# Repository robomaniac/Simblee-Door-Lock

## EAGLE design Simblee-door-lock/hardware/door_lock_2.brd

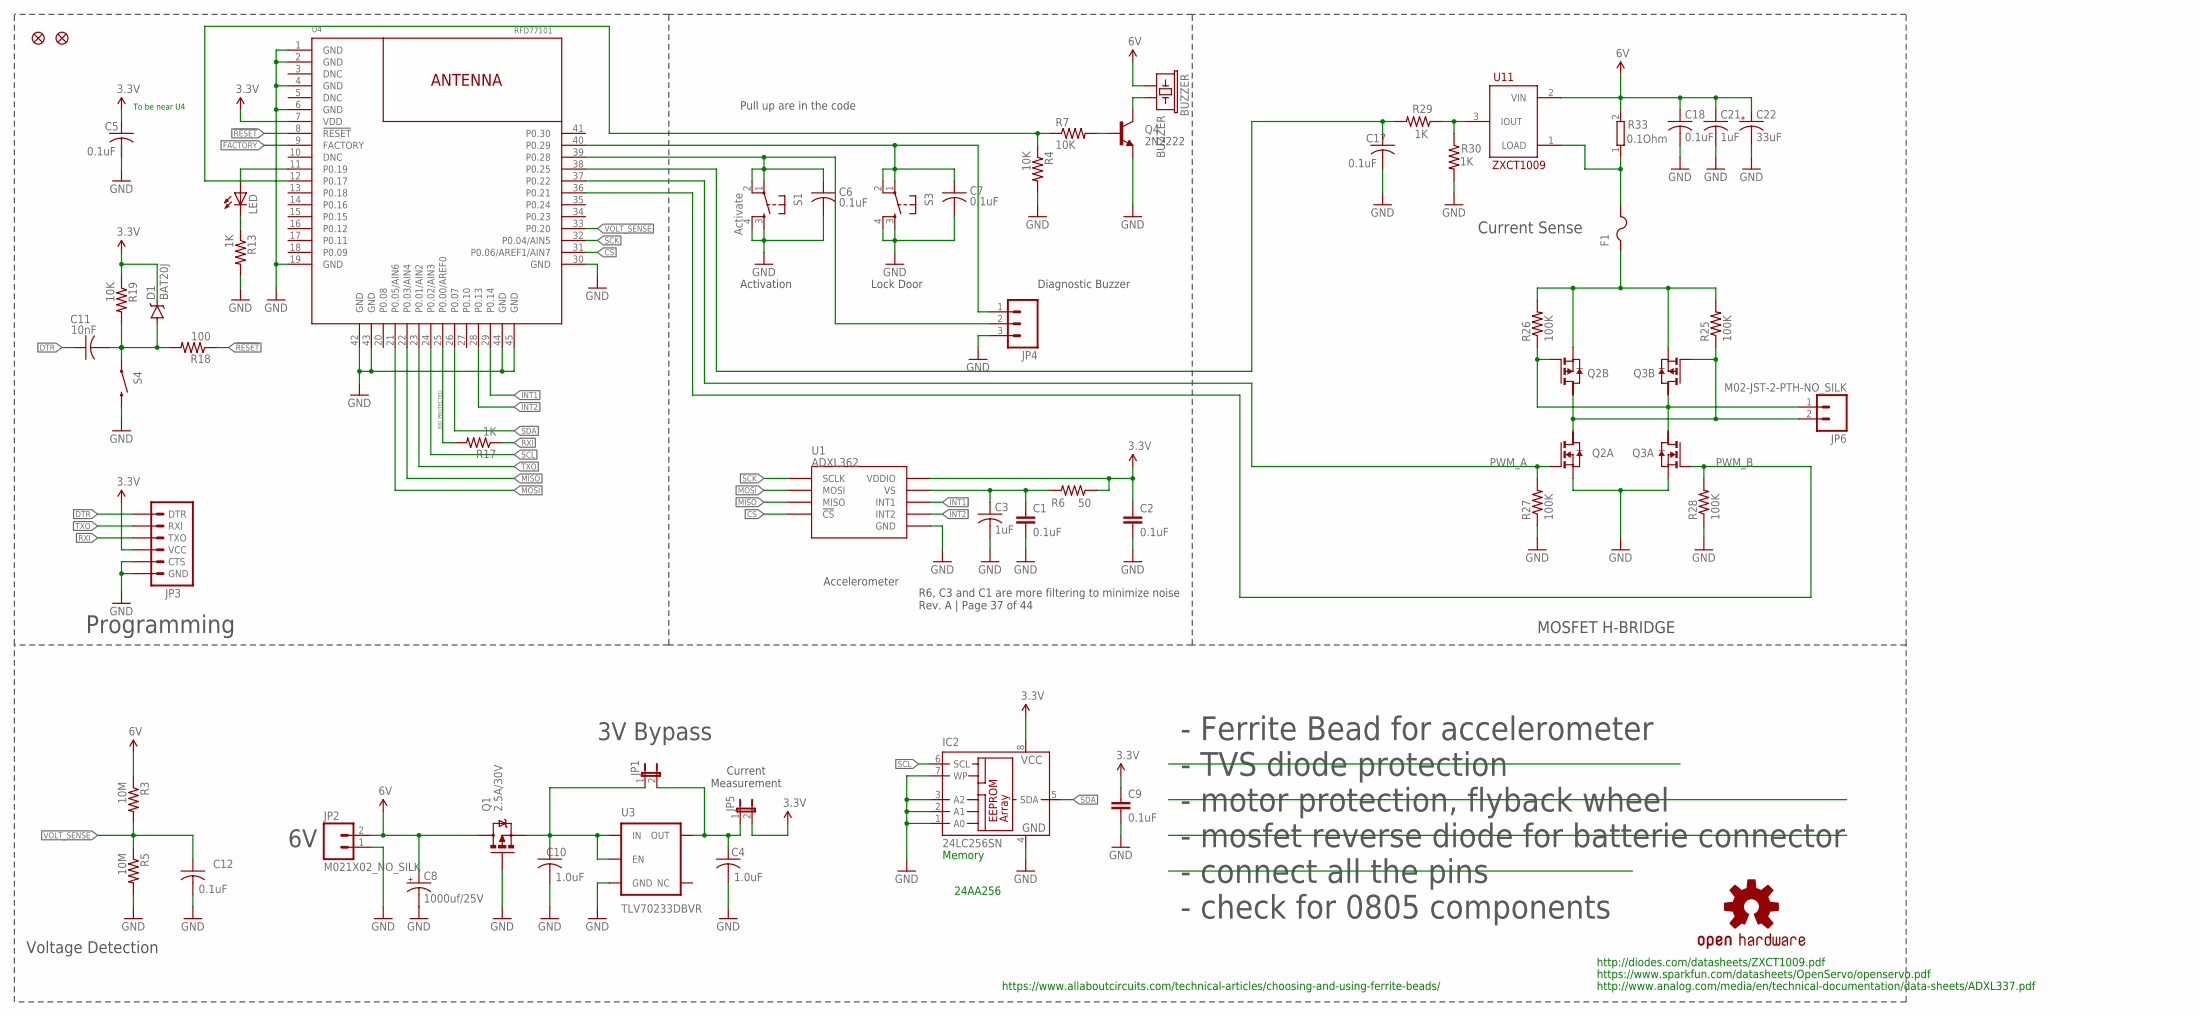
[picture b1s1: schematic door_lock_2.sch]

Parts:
BUZZER: BUZZER; BUZZER-12MM-NS
C1, C2, C9: 0.1uF; 0805
C3, C21: 1uF; C0805
C4, C10: 1.0uF; C0805
C5, C6, C7, C12, C17, C18: 0.1uF; C0805
C8: 1000uf/25V; CPOL-RADIAL-1000UF-25V-KIT
C11: 10nF; C0805
C22: 33uF; EIA3528
D1: BAT20J; SOD-323
F1: PTCFUSE-1812; 1812
IC2: 24LC256SN; SO-08
JP1: JUMPER-2SMD-NO; SJ_2S-NO
JP2: M021X02_NO_SILK; 1X02_NO_SILK
JP3: ARDUINO_SERIAL_PROGRAMPTH; 1X06
JP4: M03PTH; 1X03
JP5: JUMPER-2PTH; 1X02
JP6: M02-JST-2-PTH-NO_SILK; JST-2-PTH-NS
JP9, JP10: FIDUCIALUFIDUCIAL; MICRO-FIDUCIAL
LED: LEDCHIP-LED0805; CHIP-LED0805
Q1: 2.5A/30V; SOT23-3
Q2, Q3: PN_MOSFET-SO8; SO8
Q4: 2N2222; SOT23
R3, R5: 10M; R0805
R4, R7, R19: 10K; R0805
R6: 50; R0805
R13, R17, R29, R30: 1K; R0805
R18: 100; R0805
R25, R26, R27, R28: 100K; R0805
R33: 0.1Ohm; R1206W
S1: Activate; TACTILE-PTH
S3: TAC_SWITCHPTH; TACTILE-PTH
S4: SWITCH-MOMENTARY-2SMD; TACTILE-SWITCH-SMD
U1: ADXL362
U3: TLV70233DBVR; SOT23-5
U4: RFD77101
U11: ZXCT1009; SOT23-3
U$3: OSHW-LOGOS; OSHW-LOGO-S

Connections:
3.3V: C2.1, C5.1, C9.1, D1.C, IC2.8 (VCC), JP3.4 (VCC), JP5.2, R6.1, R19.1, U1.P$1 (VDDIO), U4.7 (VDD)
6V: BUZZER.+ (1), C8.+, C18.1, C21.1, C22.A (+), JP2.2, Q1.3 (D), R3.1, R33.2, U11.2 (VIN)
!RESET: R18.1, U4.8 (!RESET!)
ACTIVATE: C6.1, JP4.2, S1.1, S1.2, U4.39 (P0.28)
BUZZER: R4.1, R7.1, U4.12 (P0.17)
CS: U1.P$8 (!CS), U4.31 (P0.06/AREF1/AIN7)
CURSENSE: C17.1, R29.2, U4.38 (P0.25)
DTR: C11.1, JP3.1 (DTR)
FACTORY: U4.9 (FACTORY)
GND: C1.2, C2.2, C3.2, C4.2, C5.2, C6.2, C7.2, C8.-, C9.2, C10.2, C12.2, C17.2, C18.2, C21.2, C22.C (-), IC2.1 (A0), IC2.2 (A1), IC2.3 (A2), IC2.4 (GND), IC2.7 (WP), JP2.1, JP3.5 (CTS), JP3.6 (GND), JP4.3, Q1.1 (G), Q2.1 (S), Q3.1 (S), Q4.2 (E), R4.2, R5.2, R13.2, R27.1, R28.1, R30.2, S1.3, S1.4, S3.3, S3.4, S4.3 (2), U1.P$12 (GND), U1.P$13 (GND), U1.P$16 (GND), U3.2 (GND), U4.1 (GND), U4.2 (GND), U4.4 (GND), U4.6 (GND), U4.19 (GND), U4.30 (GND), U4.42 (GND), U4.43 (GND), U4.44 (GND), U4.45 (GND)
INT1: U1.P$11 (INT1), U4.29 (P0.14)
INT2: U1.P$9 (INT2), U4.28 (P0.13)
LOCK: C7.1, JP4.1, S3.1, S3.2, U4.40 (P0.29)
MISO: U1.P$7 (MISO), U4.22 (P0.03/AIN4)
MOSI: U1.P$6 (MOSI), U4.21 (P0.05/AIN6)
MOTOR_OUT_A: JP6.1, Q2.4 (G), Q3.5 (D), Q3.7 (D), R26.1
MOTOR_OUT_B: JP6.2, Q2.5 (D), Q2.7 (D), Q3.4 (G), R25.1
unnamed: C4.1, JP1.2, JP5.1, U3.5 (OUT)
unnamed: F1.2, R33.1, U11.1 (LOAD)
unnamed: C1.1, C3.1, R6.2, U1.P$14 (VS)
unnamed: Q4.1 (B), R7.2
unnamed: BUZZER.- (2), Q4.3 (C)
unnamed: C11.2, D1.A, R18.2, R19.2, S4.1
unnamed: LED.C, R13.1
unnamed: F1.1, Q2.3 (S), Q3.3 (S), R25.2, R26.2
unnamed: R29.1, R30.1, U11.3 (IOUT)
P0.10: LED.A, U4.11 (P0.19)
PWM_A: Q2.2 (G), R27.2, U4.37 (P0.22)
PWM_B: Q3.2 (G), R28.2, U4.36 (P0.21)
RXI: JP3.3 (TXO), R17.1
RXI_PROTECTED: R17.2, U4.25 (P0.00/AREF0)
SCK: U1.P$4 (SCLK), U4.32 (P0.04/AIN5)
SCL: IC2.6 (SCL), U4.24 (P0.02/AIN3)
SDA: IC2.5 (SDA), U4.26 (P0.07)
TXO: JP3.2 (RXI), U4.23 (P0.01/AIN2)
VIN1: C10.1, JP1.1, Q1.2 (S), U3.1 (IN), U3.3 (EN)
VOLT_SENSE: C12.1, R3.2, R5.1, U4.33 (P0.20)

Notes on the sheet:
Accelerometer
Activation
Diagnostic Buzzer
Lock Door
Memory
Current Measurement
To be near U4
Programming
MOSFET H-BRIDGE
Current Sense
Voltage Detection
https://www.sparkfun.com/datasheets/OpenServo/openservo.pdf
http://diodes.com/datasheets/ZXCT1009.pdf
- Ferrite Bead for accelerometer - TVS diode protection - motor protection, flyback wheel - mosfet reverse diode for batterie connector - connect all the pins - check for 0805 components
http://www.analog.com/media/en/technical-documentation/data-sheets/ADXL337.pdf
https://www.allaboutcircuits.com/technical-articles/choosing-and-using-ferrite-beads/
24AA256
3V Bypass
Pull up are in the code
R6, C3 and C1 are more filtering to minimize noise Rev. A | Page 37 of 44

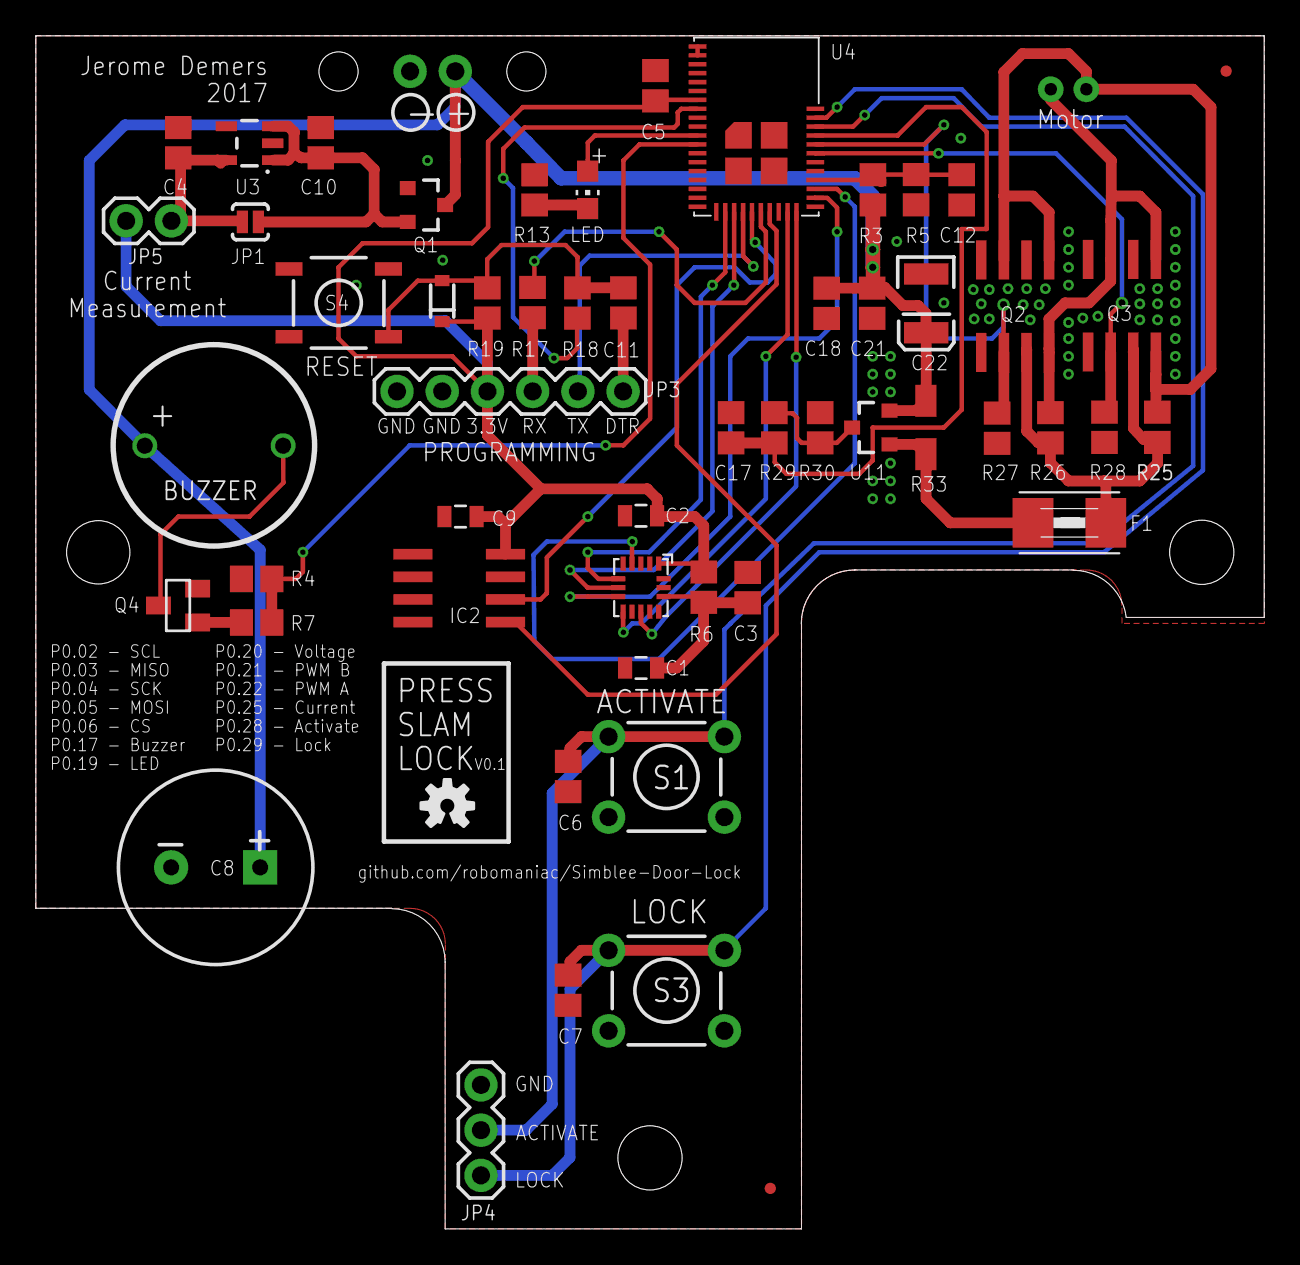
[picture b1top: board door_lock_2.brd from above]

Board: 2 copper layers, 69.0 x 67.0 mm, 57 parts (1 on the bottom side), 36 nets.

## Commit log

2017-05-22 my first commit readme message
2017-05-22 changed readme
2017-05-22 more info
2017-05-22 deltete info m
2017-05-23 added hardware folder with schematic
2017-05-23 updated schematic and PCB pictures
2017-05-23 change readme
2017-05-23 readme changed
2018-07-22 Pictures of the PCB

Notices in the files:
parts and their libraries:
SparkFun-Sensors: Licensing: CC v3.0 Share-Alike You are welcome to use this library for commercial purposes.
RFDigital: © 2015 RF Digital Corporation
SparkFun-Connectors: Licensing: Creative Commons ShareAlike 4.0 International - https://creativecommons.org/licenses/by-sa/4.0
